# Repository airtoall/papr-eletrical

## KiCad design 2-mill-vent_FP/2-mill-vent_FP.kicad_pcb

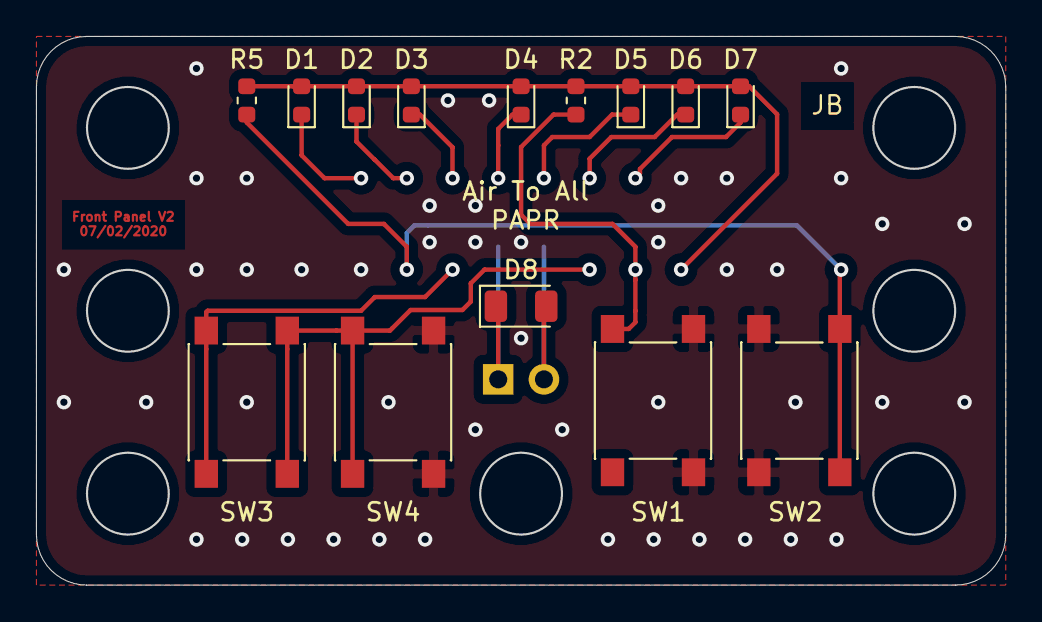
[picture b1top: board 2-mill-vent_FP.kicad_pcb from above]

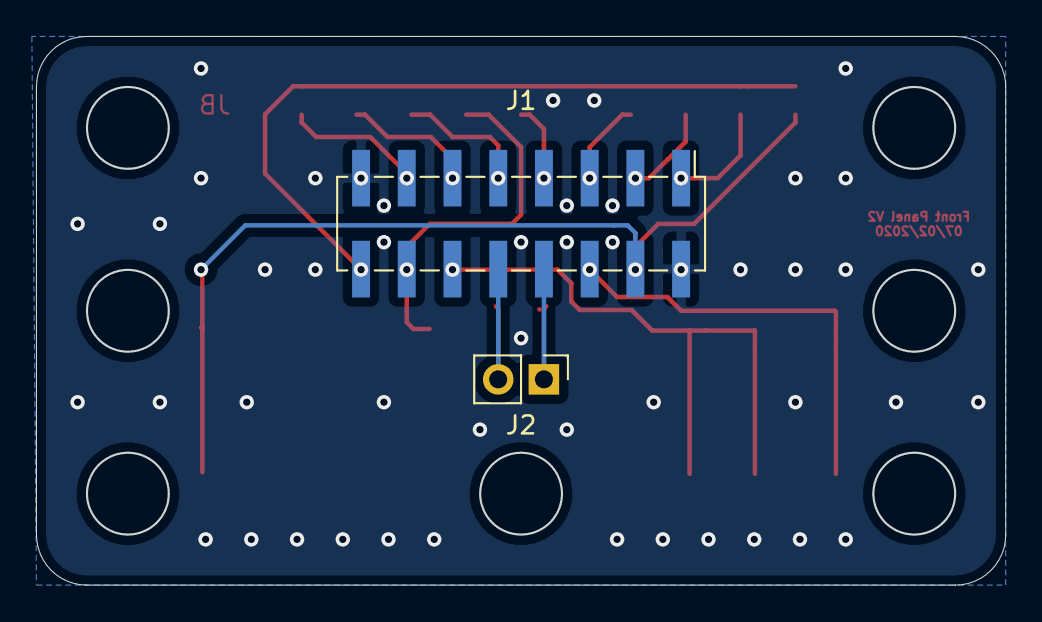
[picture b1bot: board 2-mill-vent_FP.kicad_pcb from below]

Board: 2 copper layers, 53.8 x 30.5 mm, 16 parts (2 on the bottom side), 15 nets.

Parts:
D1, D2, D3, D4, D5, D6: LED; LED_0603_1608Metric
D7: Fault; LED_0603_1608Metric
D8: 1N914; D_1206_3216Metric
J1: Front_panel_control; PinHeader_2x08_P2.54mm_Vertical_SMD
J2: Conn_01x02_Male; PinHeader_1x02_P2.54mm_Vertical
R2, R5: 100k; R_0603_1608Metric
SW1: Fan_Down; SW_SPST_PTS645
SW2: Fan_Up; SW_SPST_PTS645
SW3: Power_On; SW_SPST_PTS645
SW4: Power_off; SW_SPST_PTS645

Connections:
+5V: D1.2, D2.2, D3.2, D4.2, D5.2, D6.2, D7.2, J1.16, R2.2, R5.2
Down: J1.14, R2.1, SW1.2
GND: J1.2, J1.15, SW1.1, SW2.1, SW4.1
LED1: D1.1, J1.1
LED2: D2.1, J1.3
LED3: D3.1, J1.5
LED4: D4.1, J1.7
LED5: D5.1, J1.9
LED6: D6.1, J1.11
LED7: D7.1, J1.13
Motor+: D8.1, J1.8, J2.1
Motor-: D8.2, J1.10, J2.2
ON: J1.6, SW3.2
ON\*OFF: J1.12, SW3.1, SW4.2
Up: J1.4, R5.1, SW2.2
